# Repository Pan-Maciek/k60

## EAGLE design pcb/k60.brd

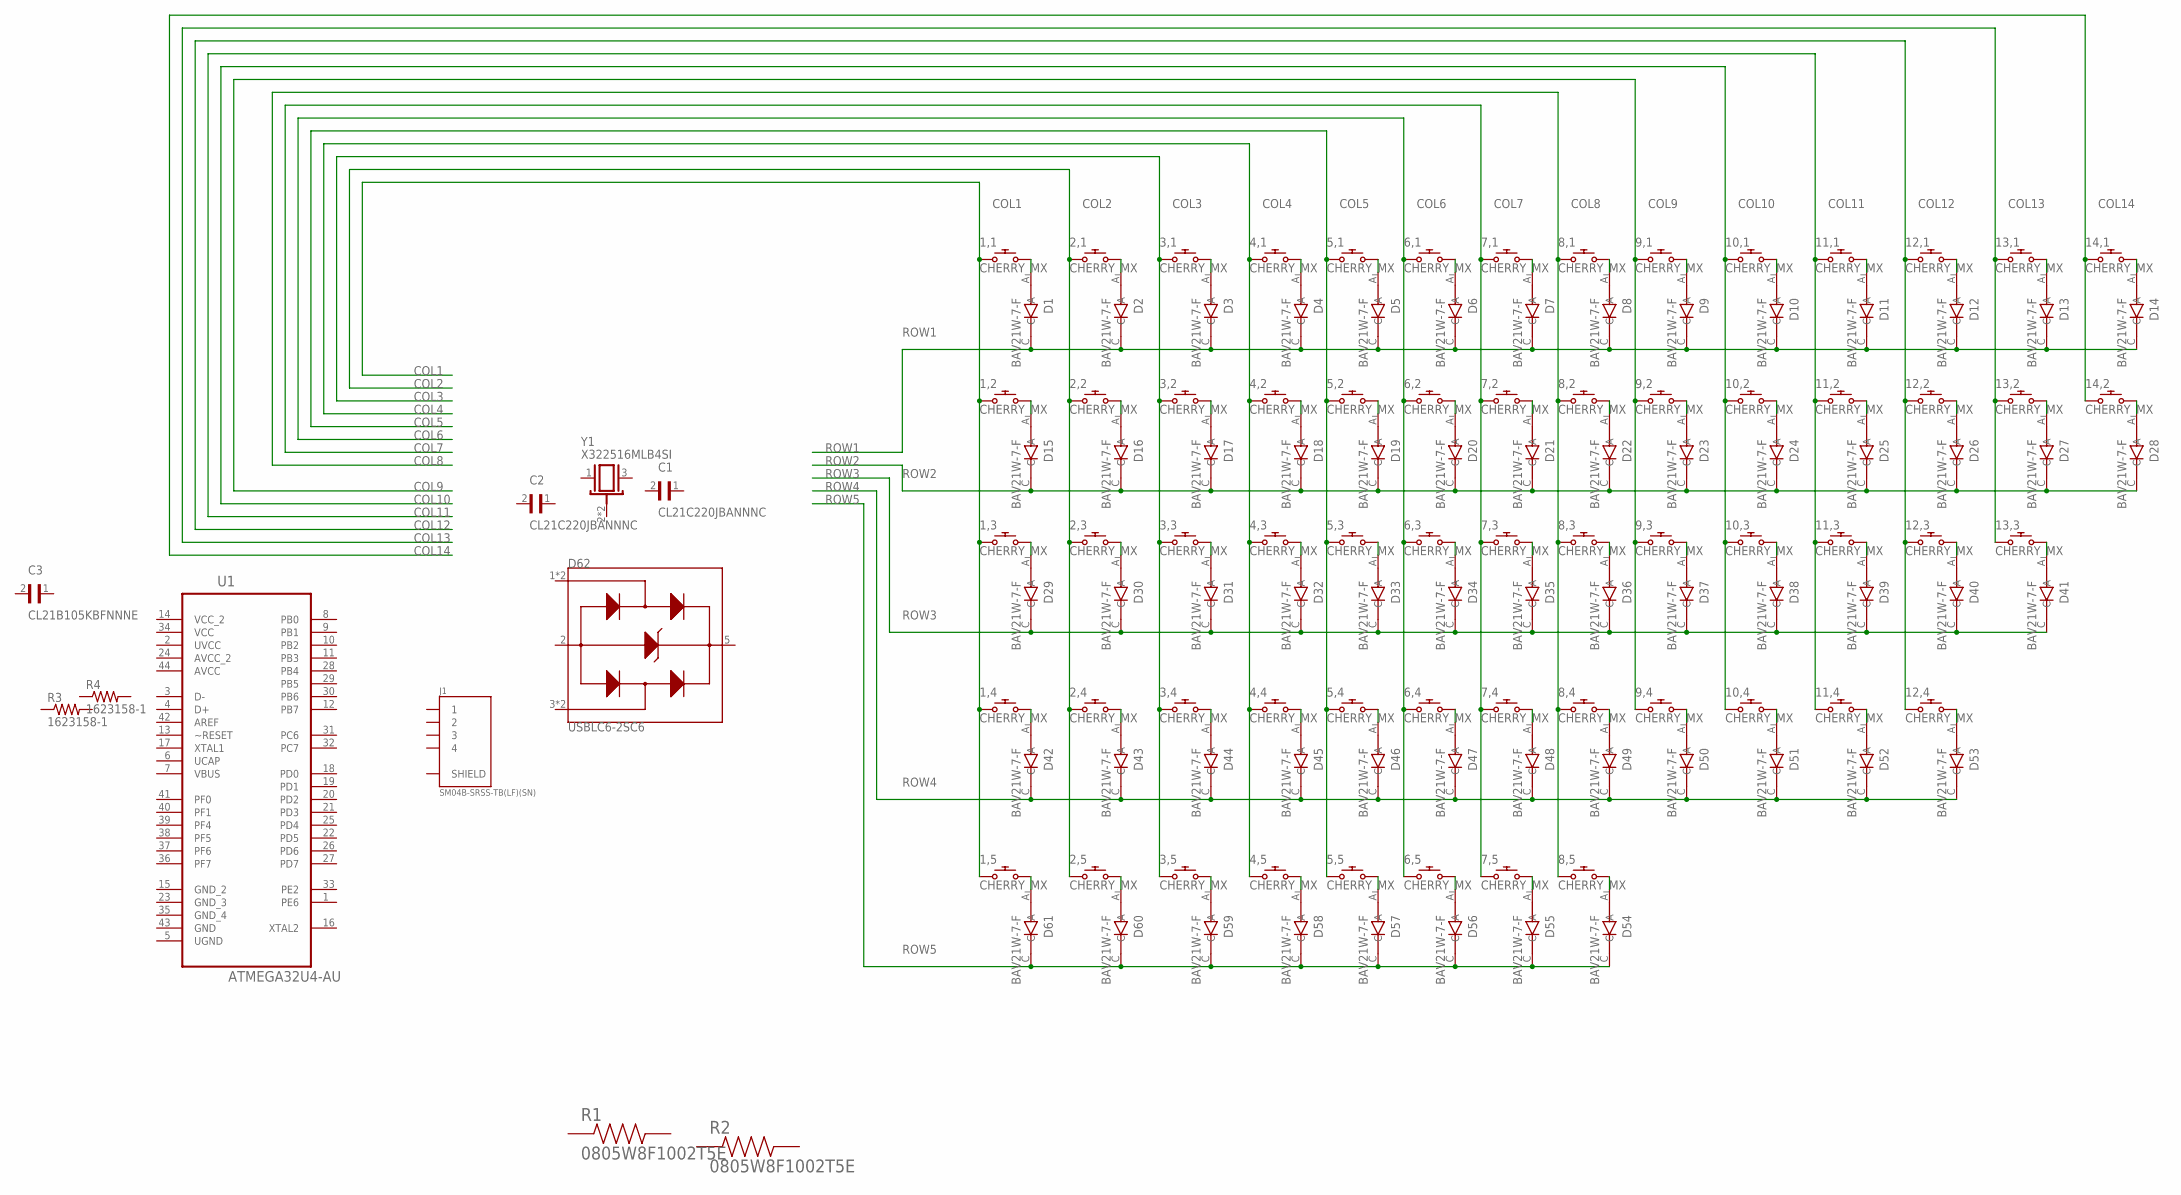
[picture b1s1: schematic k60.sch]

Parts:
1,1, 1,2, 1,3, 1,4, 1,5, 2,1, 2,2, 2,3, 2,4, 2,5, 3,1, 3,2, 3,3, 3,4, 3,5, 4,1, 4,2, 4,3, 4,4, 4,5, 5,1, 5,2, 5,3, 5,4, 5,5, 6,1, 6,2, 6,3, 6,4, 6,5, 7,1, 7,2, 7,3, 7,4, 7,5, 8,1, 8,2, 8,3, 8,4, 8,5, 9,1, 9,2, 9,3, 9,4, 10,1, 10,2, 10,3, 10,4, 11,1, 11,2, 11,3, 11,4, 12,1, 12,2, 12,3, 12,4, 13,1, 13,2, 13,3, 14,1, 14,2: CHERRY_MX
C1, C2: CL21C220JBANNNC; CAPC2012X140N
C3: CL21B105KBFNNNE; CL21B105KBFNNNE_CAPC2012X140N
D1, D2, D3, D4, D5, D6, D7, D8, D9, D10, D11, D12, D13, D14, D15, D16, D17, D18, D19, D20, D21, D22, D23, D24, D25, D26, D27, D28, D29, D30, D31, D32, D33, D34, D35, D36, D37, D38, D39, D40, D41, D42, D43, D44, D45, D46, D47, D48, D49, D50, D51, D52, D53, D54, D55, D56, D57, D58, D59, D60, D61: BAV21W-7-F; SOD3715X135N
D62: USBLC6-2SC6; SOT95P280X145-6N
J1: SM04B-SRSS-TB(LF)(SN); JST_SM04B-SRSS-TB(LF)(SN)
R1, R2: 0805W8F1002T5E; RESC2012X60N
R3, R4: 1623158-1; RESC2012X65N
U1: ATMEGA32U4-AU; QFP80P1200X1200X120-44N
Y1: X322516MLB4SI; OSC_X322516MLB4SI

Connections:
+5V: R2.2, U1.2 (UVCC), U1.7 (VBUS), U1.14 (VCC_2), U1.24 (AVCC_2), U1.34 (VCC), U1.44 (AVCC); also elsewhere on the board
COL1: 1,1.S1 (1), 1,2.S1 (1), 1,3.S1 (1), 1,4.S1 (1), 1,5.S1 (1), U1.41 (PF0)
COL2: 2,1.S1 (1), 2,2.S1 (1), 2,3.S1 (1), 2,4.S1 (1), 2,5.S1 (1), U1.40 (PF1)
COL3: 3,1.S1 (1), 3,2.S1 (1), 3,3.S1 (1), 3,4.S1 (1), 3,5.S1 (1), U1.18 (PD0)
COL4: 4,1.S1 (1), 4,2.S1 (1), 4,3.S1 (1), 4,4.S1 (1), 4,5.S1 (1), U1.19 (PD1)
COL5: 5,1.S1 (1), 5,2.S1 (1), 5,3.S1 (1), 5,4.S1 (1), 5,5.S1 (1), U1.20 (PD2)
COL6: 6,1.S1 (1), 6,2.S1 (1), 6,3.S1 (1), 6,4.S1 (1), 6,5.S1 (1), U1.21 (PD3)
COL7: 7,1.S1 (1), 7,2.S1 (1), 7,3.S1 (1), 7,4.S1 (1), 7,5.S1 (1), U1.25 (PD4)
COL8: 8,1.S1 (1), 8,2.S1 (1), 8,3.S1 (1), 8,4.S1 (1), 8,5.S1 (1), U1.22 (PD5)
COL9: 9,1.S1 (1), 9,2.S1 (1), 9,3.S1 (1), 9,4.S1 (1), U1.26 (PD6)
COL10: 10,1.S1 (1), 10,2.S1 (1), 10,3.S1 (1), 10,4.S1 (1), U1.27 (PD7)
COL11: 11,1.S1 (1), 11,2.S1 (1), 11,3.S1 (1), 11,4.S1 (1), U1.29 (PB5)
COL12: 12,1.S1 (1), 12,2.S1 (1), 12,3.S1 (1), 12,4.S1 (1), U1.30 (PB6)
COL13: 13,1.S1 (1), 13,2.S1 (1), 13,3.S1 (1), U1.12 (PB7)
COL14: 14,1.S1 (1), 14,2.S1 (1), U1.39 (PF4)
D+: D62.1 (I/O1), D62.6 (I/O1), J1.3, R4.1
D-: D62.3 (I/O2), D62.4 (I/O2), J1.2, R3.1
GND: C1.1, C2.1, C3.2, D62.2 (GND), J1.4, R1.2, U1.5 (UGND), U1.15 (GND_2), U1.23 (GND_3), U1.35 (GND_4), U1.43 (GND), Y1.2 (GND), Y1.4 (GND); also elsewhere on the board
MCU_D+: R4.2, U1.4 (D+)
MCU_D-: R3.2, U1.3 (D-)
unnamed: C3.1, U1.6 (UCAP)
unnamed: R1.1, U1.33 (PE2)
unnamed: 1,1.S2 (2), D1.A
unnamed: 2,1.S2 (2), D2.A
unnamed: 3,1.S2 (2), D3.A
unnamed: 4,1.S2 (2), D4.A
unnamed: 5,1.S2 (2), D5.A
unnamed: 6,1.S2 (2), D6.A
unnamed: 7,1.S2 (2), D7.A
unnamed: 8,1.S2 (2), D8.A
unnamed: 9,1.S2 (2), D9.A
unnamed: 10,1.S2 (2), D10.A
unnamed: 11,1.S2 (2), D11.A
unnamed: 12,1.S2 (2), D12.A
unnamed: 13,1.S2 (2), D13.A
unnamed: 14,1.S2 (2), D14.A
unnamed: 1,2.S2 (2), D15.A
unnamed: 2,2.S2 (2), D16.A
unnamed: 3,2.S2 (2), D17.A
unnamed: 4,2.S2 (2), D18.A
unnamed: 5,2.S2 (2), D19.A
unnamed: 6,2.S2 (2), D20.A
unnamed: 7,2.S2 (2), D21.A
unnamed: 8,2.S2 (2), D22.A
unnamed: 9,2.S2 (2), D23.A
unnamed: 10,2.S2 (2), D24.A
unnamed: 11,2.S2 (2), D25.A
unnamed: 12,2.S2 (2), D26.A
unnamed: 13,2.S2 (2), D27.A
unnamed: 1,3.S2 (2), D29.A
unnamed: 2,3.S2 (2), D30.A
unnamed: 3,3.S2 (2), D31.A
unnamed: 4,3.S2 (2), D32.A
unnamed: 5,3.S2 (2), D33.A
unnamed: 6,3.S2 (2), D34.A
unnamed: 7,3.S2 (2), D35.A
unnamed: 8,3.S2 (2), D36.A
unnamed: 9,3.S2 (2), D37.A
unnamed: 10,3.S2 (2), D38.A
unnamed: 11,3.S2 (2), D39.A
unnamed: 12,3.S2 (2), D40.A
unnamed: 13,3.S2 (2), D41.A
unnamed: 14,2.S2 (2), D28.A
unnamed: 1,4.S2 (2), D42.A
unnamed: 2,4.S2 (2), D43.A
unnamed: 3,4.S2 (2), D44.A
unnamed: 4,4.S2 (2), D45.A
unnamed: 5,4.S2 (2), D46.A
unnamed: 6,4.S2 (2), D47.A
unnamed: 7,4.S2 (2), D48.A
unnamed: 8,4.S2 (2), D49.A
unnamed: 9,4.S2 (2), D50.A
unnamed: 10,4.S2 (2), D51.A
unnamed: 11,4.S2 (2), D52.A
unnamed: 12,4.S2 (2), D53.A
unnamed: 1,5.S2 (2), D61.A
unnamed: 2,5.S2 (2), D60.A
unnamed: 3,5.S2 (2), D59.A
unnamed: 4,5.S2 (2), D58.A
unnamed: 5,5.S2 (2), D57.A
unnamed: 6,5.S2 (2), D56.A
unnamed: 7,5.S2 (2), D55.A
unnamed: 8,5.S2 (2), D54.A
RESET: R2.1, U1.13 (~RESET); also elsewhere on the board
ROW1: D1.C, D2.C, D3.C, D4.C, D5.C, D6.C, D7.C, D8.C, D9.C, D10.C, D11.C, D12.C, D13.C, D14.C, U1.8 (PB0)
ROW2: D15.C, D16.C, D17.C, D18.C, D19.C, D20.C, D21.C, D22.C, D23.C, D24.C, D25.C, D26.C, D27.C, D28.C, U1.9 (PB1)
ROW3: D29.C, D30.C, D31.C, D32.C, D33.C, D34.C, D35.C, D36.C, D37.C, D38.C, D39.C, D40.C, D41.C, U1.10 (PB2)
ROW4: D42.C, D43.C, D44.C, D45.C, D46.C, D47.C, D48.C, D49.C, D50.C, D51.C, D52.C, D53.C, U1.11 (PB3)
ROW5: D54.C, D55.C, D56.C, D57.C, D58.C, D59.C, D60.C, D61.C, U1.28 (PB4)
VBUS: D62.5 (VBUS), J1.1; also elsewhere on the board
XTAL1: C1.2, U1.17 (XTAL1), Y1.1
XTAL2: C2.2, U1.16 (XTAL2), Y1.3

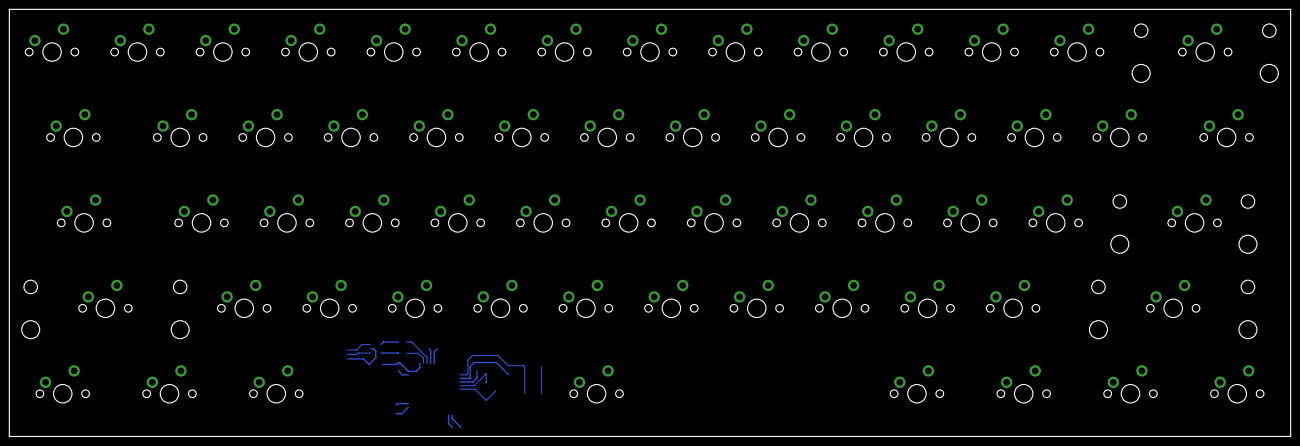
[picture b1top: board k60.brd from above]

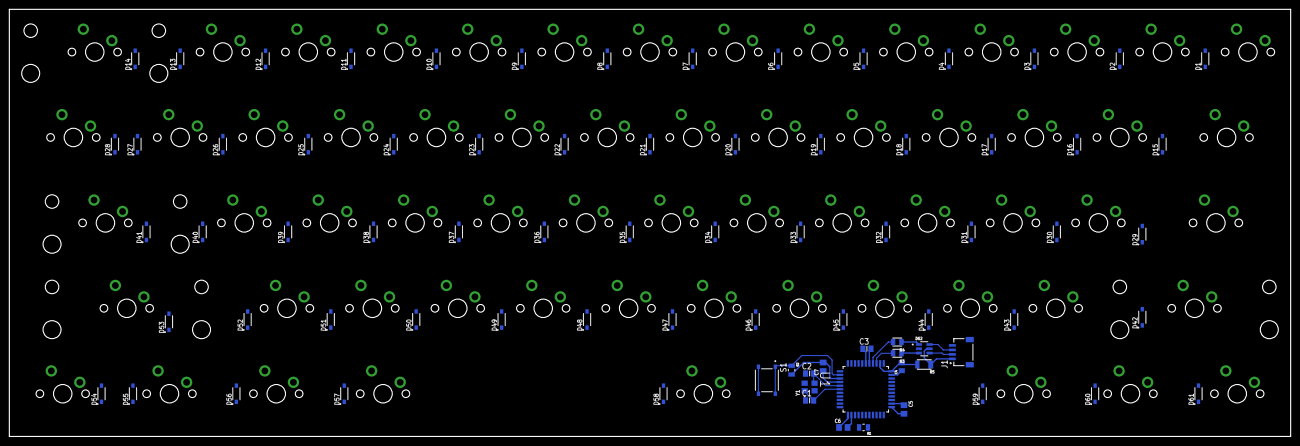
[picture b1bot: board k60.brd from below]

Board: 2 copper layers, 285.0 x 95.0 mm, 139 parts (78 on the bottom side), 92 nets.

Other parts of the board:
C4: CL21A106KAYNNNE; CAPC2012X135N
C5, C6, C7: CC0805KRX7R9BB104; CAPC2012X70
R5: NSMD050-24V; RESC3115X65N
S1: TS-1187A-B-A-B; SW_TS-1187A-B-A-B

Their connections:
+5V: C4.2, C5.2, C6.2, C7.2, R5.2; also elsewhere on the board
GND: C4.1, C5.1, C6.1, C7.1, S1.C, S1.D; also elsewhere on the board
RESET: S1.A, S1.B; also elsewhere on the board
VBUS: R5.1; also elsewhere on the board

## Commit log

2021-04-17 basic board outline
    TODO:
    * Center LShift, Enter, RShift and whole ROW5
    * Place stabilizer holes
    * Add mounting points for case
    * Connect crystal
    * Add fuse
2021-04-17 aligned missaligned keys
2021-04-17 fixed board dimensions, mx_switch
    original mx_switch component was using layer 20 (Dimension)
    layer 20 is used to determine pcb surface
    moved outline from layer 20 to layer 51 (tDocu)
    hint:
    to update component lib add new component from this lib in .sch file
    added rough pcb dimension and mounting points for stabilizers
2021-04-19 changed lib to custom k60 lib
2021-04-19 moved to positive coordinates
2021-04-20 schematic cleanup, connected important compoonents
    added power stabilization (10uF, 1uF)
2021-05-18 some initial project pieces
2021-05-18 project update
2021-05-25 prototype works
2021-05-25 HID v0.1
2021-05-25 layer switching nie działa
2021-06-07 done
